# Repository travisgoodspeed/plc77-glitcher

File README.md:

Howdy y'all,

As I write this in 2021, glitching is all the rage in hardware
security again, but twenty years ago in the satellite TV cracking
community it was just as popular, with hand-etched PCBs of
through-hole components being used to glitch smart cards and freely
watch TV.

As Tripod begins to bitrot and this history slowly becomes lost to us,
I thought I'd grab an old glitcher from a [Tripod
website](http://dark-agent_drdss.tripod.com/drdss/id7.html), convert
it to Kicad, and maybe assemble a few glitchers from that age.  This
one is by LPC77, dating from April of 2001.

--Travis

## Organization

The root directory is a [Kicad](https://www.kicad.org/) project,
restored from the original design but without modernizations such as
surface-mount componenets that would alter its asthetics.

The `past` directory contains the published source files, originally
in Eagle's old binary format.  I used Eagle 6.6.0 under Wine to
convert the files into the modern XML format, which Kicad can freely
import.

## Original README Follows

Revisons:
I have increased the length of the circuit board by 1/2 inch 
to allow for a less cluttered layout.

I moved the surface mount resistors nearer to the thru hole types.

I also (the Most Significant change) modified the oscilator circuit
to add a resistor(R6) and change the value of R1, making the output
wave form much better.

Parts list and Notes

```
1 ISO card socket of your choosing
1 9 pin female D sum min connector (X2)
2 1n4004 diodes (D2, D3)
2 1n914 or 1n4148 diodes (D4, D5)
1 red/dreen led (two lead type) (D1)
1 90S2313p-10 atmel processor (IC1)programmed with bl.hex
1 MAX232 (IC3)
1 74HC00 (IC4) 
1 7405 (IC2)
1 7805T (U1)
1 bridge rectifyer (B1)
2 .1uf cap (C1, C3)
2 27pf cap (C4, C5)
1 35uf to 100 uf Cap 16v min (C2)
4 10 uf 16v cap (C6, C8, C9, C10)
2 430 to 475 ohm resister(R3 or R3a,R4 or R4a)
1 1 Meg ohm resister (R1 or R1a)
1 33ohm 1/2 watt resister (R2)
1 1K to 2.2K resister (R5 or R5a)
1 2.2K resister (R6 or R6a)
1 3.57595 mhz Crystal (Q1)
```

This programmer is intended to be used as a standalone Phoenix type
ISO programmer with the ability to use the Atmel Chip from the
Simpleboot product to allow operation with H cards that have suffered
the Black Sunday ECM.

If non Glitching operation is desired, simply do not install the Atmel
IC and put a jumper wire from pin 12 to 13 of that atmels socket.

It is designed to be built on a single sided pcb but there are a few
jumpers that must be installed.

The original one used surface mounted resister and i have added
provisions for thru hole parts, use one or the other not both!

I recommend that all the ICs be socketed.

If you wish to power the programmer from the PC, use a pc power
extension from Radio Shack and cut off one of the male plugs and
attach the red wire to the pad which goes to the diode and the black
wires to the two center pads, the yellow wire it not used but may be
soldered to the pad provided.

If powered from PC, the bridge, regulator and associated parts may be
removed.

I designed the layout to fit the four inch wide opening typical of the
diskette drive in a PC.  I mounted a programer on the plastic type
adapter used to mount a diskette drive in a 5 1/4 inch bay of a PC
with great success.

In an AT type PC it is possible to attach the comm port from the
motherboard to the internally mounted by moving the connector from the
pc's back panel or slot cover. This make for a very neat Emulation
setup.

I have added a slightly modified layout to the package that may be a
little easier to build as it is a little larger and not so
crowded. Take a look at Glitchprog1LedB.brd, the schematic is
identical so i did not duplicate it.

This is my first attempt at releasing a design so pardon my
errors. Your comments are appreiciated, I will learn from them.

 PLC77

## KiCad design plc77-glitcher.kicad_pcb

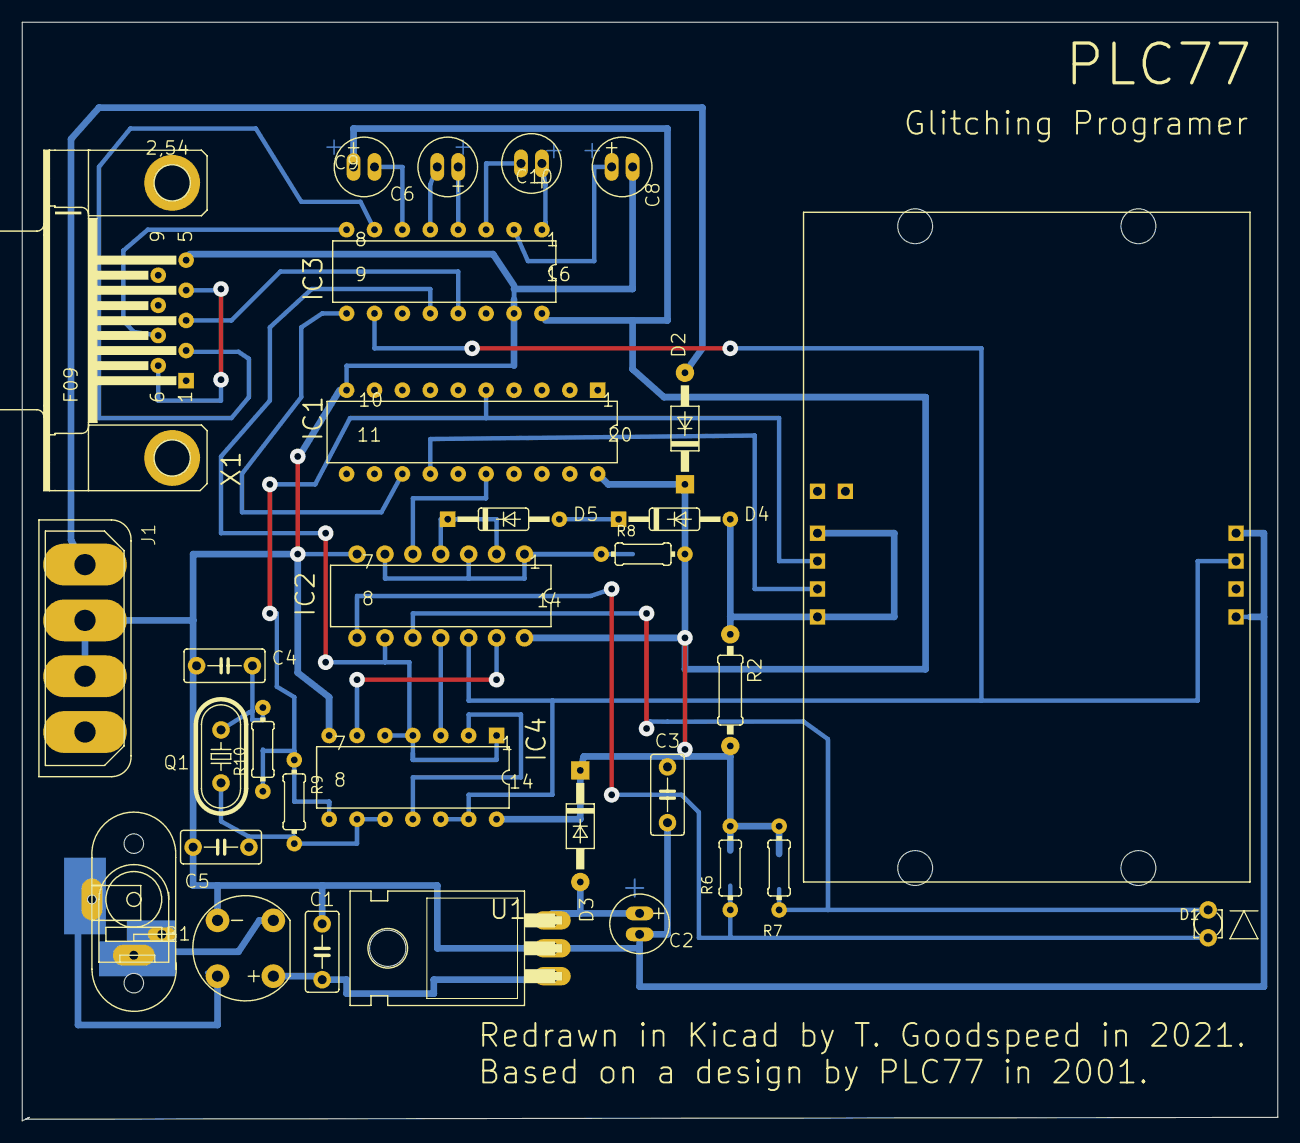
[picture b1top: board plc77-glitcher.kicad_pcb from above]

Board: 16 copper layers, 114.3 x 100.0 mm, 36 parts (0 on the bottom side), 34 nets.

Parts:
B1: RB1A
C1, C3: .1uf; C5B3
C2: 35uf; E2,0-5
C4, C5: 27pf; C5B3
C6, C8, C9, C10: 10uf; E2,0-5
CDR1: CHEAPREADR; CHEAPREA
D1: Red/Grn LED; LED2
D2, D3: 1N4004; DO41-10
D4, D5: 1N4148; DO35-10
IC1: AT90S2313P; DIL20
IC2: 7405; DIL14
IC3: MAX232; DIL16
IC4: 74HC00N; DIL14
J1: FLOPPY-4
Q1: 3.5795 MHZ; HC49U-V
R1: 1M; 1210
R2: 0207_10
R3, R4: 470; 1210
R5: R2010
R6, R7, R8, R9, R10: 0204_7
R11: 2.2k; M1206
U1: 7805T; TO220H
U$7: POWER1
X1: F09HP

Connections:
GND: B1.-, C1.1, C2.-, C3.1, C4.1, C5.1, C8.-, CDR1.P$9, CDR1.P$12, IC1.10, IC2.7, IC3.15, IC4.7, J1.3, U1.2, X1.5
unnamed: C9.-, IC3.5
unnamed: IC2.1, IC2.3, IC2.6, R5.1, R8.1
unnamed: C10.-, IC3.3
unnamed: C10.+, IC3.1
unnamed: C9.+, IC3.4
unnamed: C6.-, IC3.6
unnamed: C8.+, IC3.2
unnamed: C4.2, Q1.1, R10.2, R11.2
unnamed: IC1.13, IC3.9
unnamed: CDR1.P$3, IC1.5, IC4.8, R1.1, R9.1, R10.1, R11.1
unnamed: D4.K, D5.A
unnamed: CDR1.P$2, IC1.14
unnamed: IC3.8, X1.7
unnamed: B1.+, C1.2, U1.1
unnamed: X1.4, X1.6
unnamed: D1.A, IC2.8, R4.1, R6.1
unnamed: CDR1.P$10, IC2.12, IC3.10, IC4.12, IC4.13
unnamed: CDR1.P$1, CDR1.P$4, D4.A, R2.1
unnamed: IC3.7, X1.2
unnamed: D5.K, IC2.2, IC2.4
unnamed: IC2.9, IC3.12, IC4.1, IC4.4, IC4.5
unnamed: D1.K, IC2.10, R3.1, R7.2
unnamed: B1.AC1, U$7.P$2
unnamed: B1.AC2, U$7.P$3, U$7.P$4
unnamed: IC2.13, IC4.6
unnamed: C5.2, IC4.9, IC4.10, Q1.2, R1.2, R9.2
unnamed: IC4.2, IC4.11
unnamed: IC3.13, X1.3
unnamed: IC1.16, IC2.5
unnamed: IC2.11, IC4.3
unnamed: C2.+, D3.A, U1.3
unnamed: D2.A, J1.4
VCC: C3.2, C6.+, D2.K, D3.K, IC1.20, IC2.14, IC3.16, IC4.14, R2.2, R3.2, R4.2, R5.2, R6.2, R7.1, R8.2

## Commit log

2021-09-09 First post.
2021-09-09 Original schematc in old Eagle format.
2021-09-09 Basic README.
2021-09-09 Eagle 6.6.0 conversion of the original files.
2021-09-09 Initial import to Kicad. Don't know if backannotation matches yet.
2021-09-09 Some 3D models and silkscreening.
2021-09-09 Rest of the README.
2021-09-09 More 3D models, minor silkscreen changes.
2021-09-09 More 3D packages.
2021-09-10 3D model for the smart card holder.
2021-09-11 Label placement.
2021-12-14 Photo of the glitcher.
2021-12-14 Update README to include photo.
2024-04-21 Snapping to grid.
